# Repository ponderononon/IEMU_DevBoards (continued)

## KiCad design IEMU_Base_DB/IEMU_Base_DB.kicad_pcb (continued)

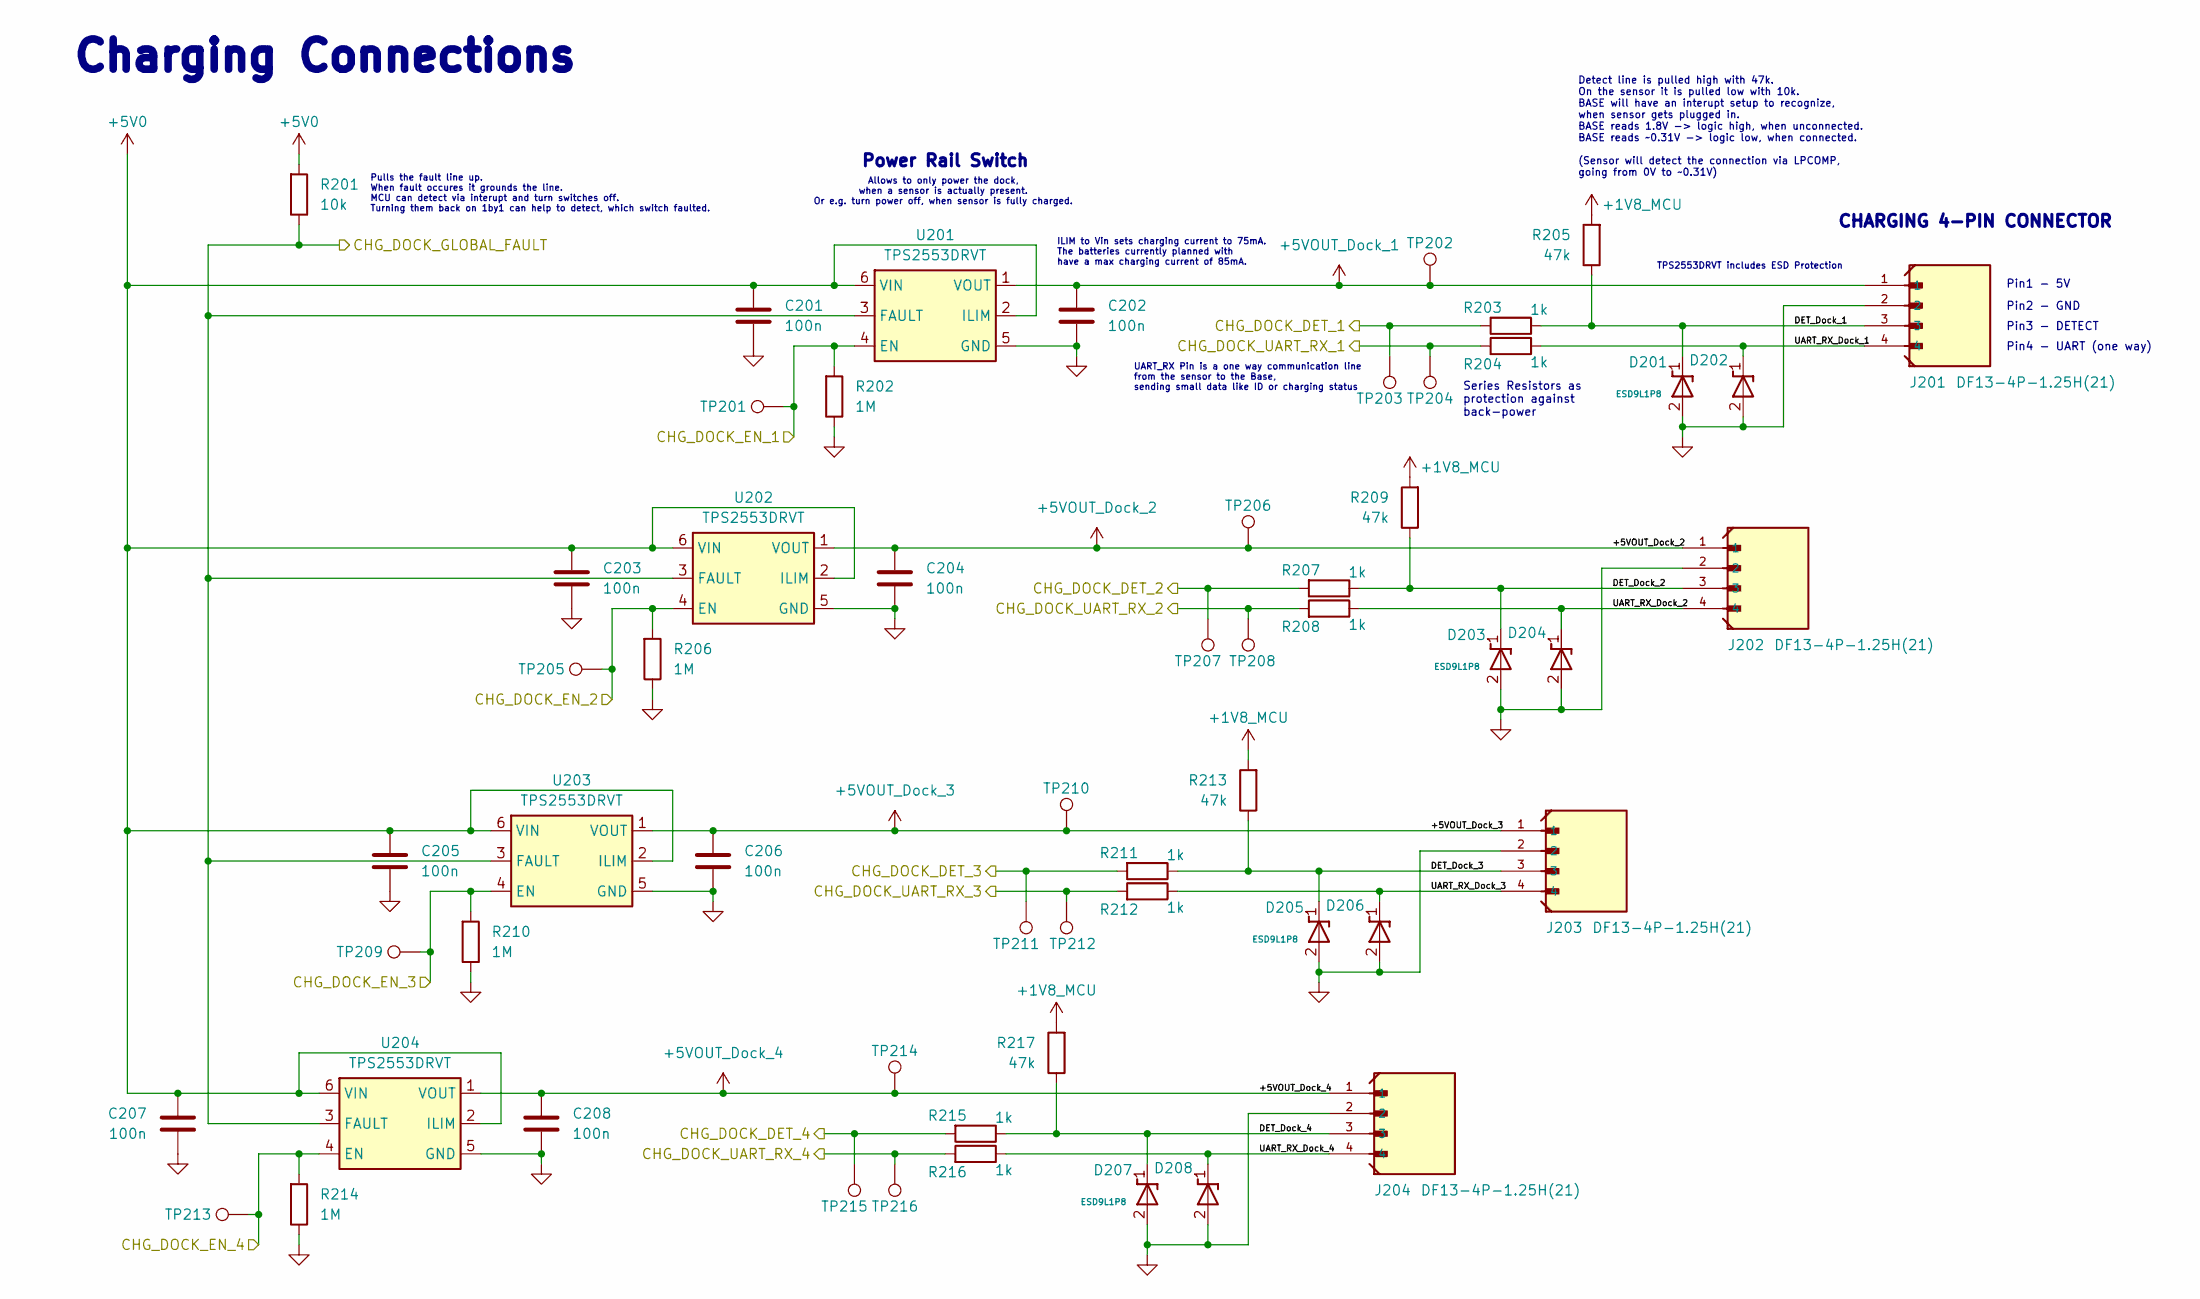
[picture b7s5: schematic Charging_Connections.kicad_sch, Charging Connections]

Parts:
C201, C202, C203, C204, C205, C206, C207, C208: 100n; C_0402_1005Metric; Manufacturer_Part_Number CL05B104KB54PNC; LCSC C307331
D201, D202, D203, D204, D205, D206, D207, D208: ESD9L1P8; D_SOD-882; Manufacturer_Part_Number ESD9L1P8; LCSC C6244607
J201, J202, J203, J204: DF13-4P-1.25H(21); Manufacturer_Part_Number DF13-4P-1.25H(21); LCSC C597872
R201: 10k; R_0402_1005Metric; Manufacturer_Part_Number 0402WGF1002TCE; LCSC C25744
R202, R206, R210, R214: 1M; R_0402_1005Metric; Manufacturer_Part_Number 0402WGF1004TCE; LCSC C26083
R203, R204, R207, R208, R211, R212, R215, R216: 1k; R_0402_1005Metric; Manufacturer_Part_Number 0402WGF1001TCE; LCSC C11702
R205, R209, R213, R217: 47k; R_0402_1005Metric; Manufacturer_Part_Number 0402WGF4702TCE; LCSC C25792
TP201, TP202, TP203, TP204, TP205, TP206, TP207, TP208, TP209, TP210, TP211, TP212, TP213, TP214, TP215, TP216: TestPoint_Pad_D1.0mm
U201, U202, U203, U204: TPS2553DRVT; WSON-6-1EP_2x2mm_P0.65mm_EP1x1.6mm; Manufacturer_Part_Number TPS2553DRVT; LCSC C2871420

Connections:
+1V8_MCU: R205.1, R209.1, R213.1, R217.1; also elsewhere on the board
+5V0: C201.1, C203.1, C205.1, C207.1, R201.1, U201.2 (ILIM), U201.6 (VIN), U202.2 (ILIM), U202.6 (VIN), U203.2 (ILIM), U203.6 (VIN), U204.2 (ILIM), U204.6 (VIN); also elsewhere on the board
+5VOUT_Dock_1: C202.1, J201.1, TP202.1, U201.1 (VOUT); also elsewhere on the board
+5VOUT_Dock_2: C204.1, J202.1, TP206.1, U202.1 (VOUT); also elsewhere on the board
+5VOUT_Dock_3: C206.1, J203.1, TP210.1, U203.1 (VOUT); also elsewhere on the board
+5VOUT_Dock_4: C208.1, J204.1, TP214.1, U204.1 (VOUT); also elsewhere on the board
/2_Charging_Connections/CHG_DOCK_DET_1: R203.1, TP203.1; also elsewhere on the board
/2_Charging_Connections/CHG_DOCK_DET_2: R207.1, TP207.1; also elsewhere on the board
/2_Charging_Connections/CHG_DOCK_DET_3: R211.1, TP211.1; also elsewhere on the board
/2_Charging_Connections/CHG_DOCK_DET_4: R215.1, TP215.1; also elsewhere on the board
/2_Charging_Connections/CHG_DOCK_EN_1: R202.1, TP201.1, U201.4 (EN); also elsewhere on the board
/2_Charging_Connections/CHG_DOCK_EN_2: R206.1, TP205.1, U202.4 (EN); also elsewhere on the board
/2_Charging_Connections/CHG_DOCK_EN_3: R210.1, TP209.1, U203.4 (EN); also elsewhere on the board
/2_Charging_Connections/CHG_DOCK_EN_4: R214.1, TP213.1, U204.4 (EN); also elsewhere on the board
/2_Charging_Connections/CHG_DOCK_GLOBAL_FAULT: R201.2, U201.3 (FAULT), U202.3 (FAULT), U203.3 (FAULT), U204.3 (FAULT); also elsewhere on the board
/2_Charging_Connections/CHG_DOCK_UART_RX_1: R204.1, TP204.1; also elsewhere on the board
/2_Charging_Connections/CHG_DOCK_UART_RX_2: R208.1, TP208.1; also elsewhere on the board
/2_Charging_Connections/CHG_DOCK_UART_RX_3: R212.1, TP212.1; also elsewhere on the board
/2_Charging_Connections/CHG_DOCK_UART_RX_4: R216.1, TP216.1; also elsewhere on the board
/2_Charging_Connections/DET_Dock_1: D201.1 (I/O), J201.3, R203.2, R205.2
/2_Charging_Connections/DET_Dock_2: D203.1 (I/O), J202.3, R207.2, R209.2
/2_Charging_Connections/DET_Dock_3: D205.1 (I/O), J203.3, R211.2, R213.2
/2_Charging_Connections/DET_Dock_4: D207.1 (I/O), J204.3, R215.2, R217.2
/2_Charging_Connections/UART_RX_Dock_1: D202.1 (I/O), J201.4, R204.2
/2_Charging_Connections/UART_RX_Dock_2: D204.1 (I/O), J202.4, R208.2
/2_Charging_Connections/UART_RX_Dock_3: D206.1 (I/O), J203.4, R212.2
/2_Charging_Connections/UART_RX_Dock_4: D208.1 (I/O), J204.4, R216.2
GND: C201.2, C202.2, C203.2, C204.2, C205.2, C206.2, C207.2, C208.2, D201.2 (GND), D202.2 (GND), D203.2 (GND), D204.2 (GND), D205.2 (GND), D206.2 (GND), D207.2 (GND), D208.2 (GND), J201.2, J202.2, J203.2, J204.2, R202.2, R206.2, R210.2, R214.2, U201.5 (GND), U201.7 (GND), U202.5 (GND), U202.7 (GND), U203.5 (GND), U203.7 (GND), U204.5 (GND), U204.7 (GND); also elsewhere on the board

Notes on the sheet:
Series Resistors as protection against back-power
Allows to only power the dock, when a sensor is actually present. Or e.g. turn power off, when sensor is fully charged.
ILIM to Vin sets charging current to 75mA. The batteries currently planned with have a max charging current of 85mA.
Pin2 - GND
Charging Connections
Detect line is pulled high with 47k. On the sensor it is pulled low with 10k. BASE will have an interupt setup to recognize, when sensor gets plugged in. BASE reads 1.8V -> logic high, when unconnected. BASE reads ~0.31V -> logic low, when connected. (Sensor will detect the connection via LPCOMP, g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
TPS2553DRVT includes ESD Protection
Pin4 - UART (one way)
Pin3 - DETECT
UART_RX Pin is a one way communication line from the sensor to the Base, sending small data like ID or charging status
CHARGING 4-PIN CONNECTOR
Pulls the fault line up. When fault occures it grounds the line. MCU can detect via interupt and turn switches off. Turning them back on 1by1 can help to detect, which switch faulted.
Pin1 - 5V
Power Rail Switch

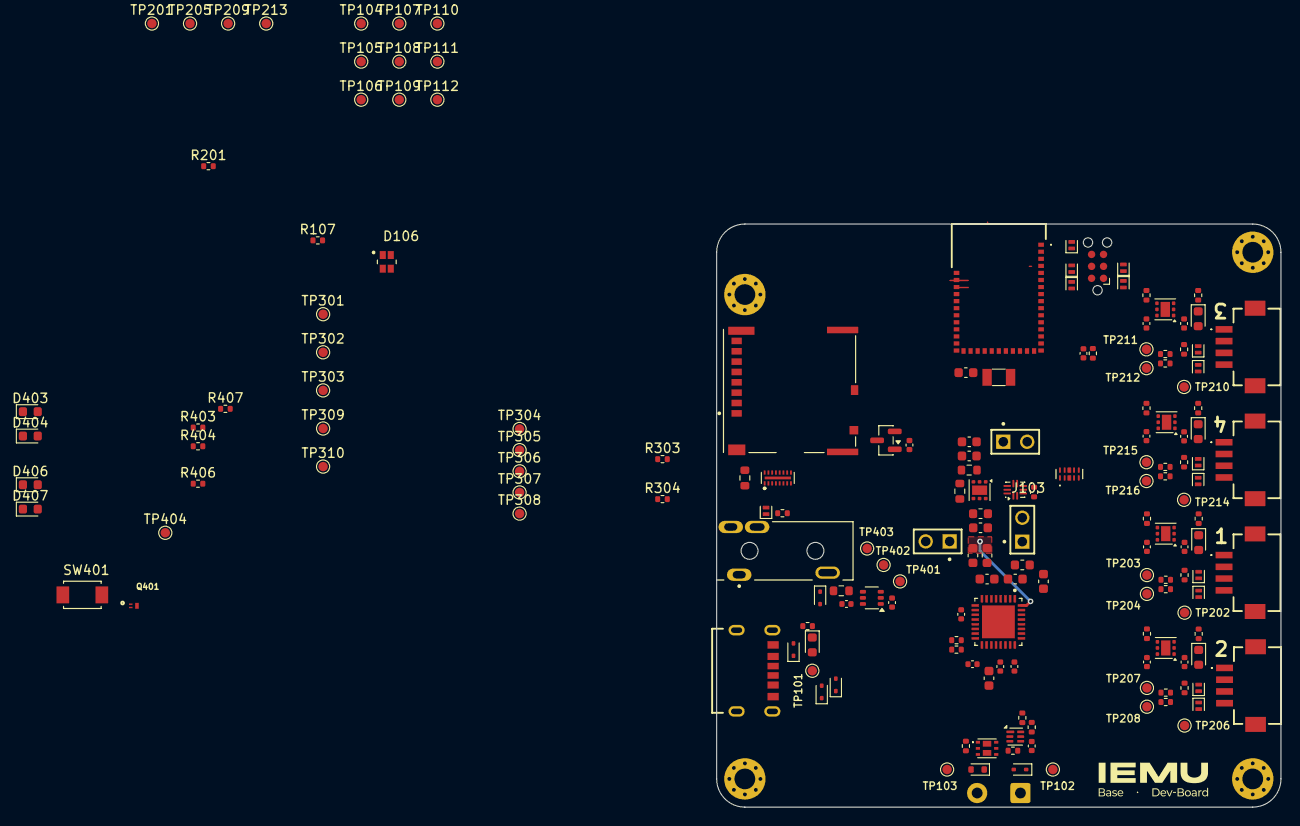
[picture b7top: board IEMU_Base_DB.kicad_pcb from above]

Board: 4 copper layers, 60.0 x 62.0 mm, 176 parts (0 on the bottom side), 95 nets.

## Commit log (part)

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2026-05-08 initial commit of the IEMU-Sensor and Base Kicad files
2026-05-08 changed reusable_libraries folder to name IEMU_Shared_Libraries and also introduced more relative paths for the library components to make the links more robust
2026-05-08 added hall effect sensor for lid detection
2026-05-08 corrected mcu-sheet file name
2026-05-08 added a short ReadMe
2026-05-08 removed the r-studio file, that got created by accidentally opening the readme with R
2026-05-08 swapped the coin cell vibration actuator pins
2026-05-08 added schematic pdf for the sensor
2026-06-03 implemented changes from the review with TF and fixed lost parts in the library
2026-06-03 finished schematic revision based on TF-review by implementing sensor schematic too
2026-06-22 created the layout for the sensor (not finished)
2026-06-24 finished layout for sensor
2026-06-25 layout of base and some fixes on the sensor layout
